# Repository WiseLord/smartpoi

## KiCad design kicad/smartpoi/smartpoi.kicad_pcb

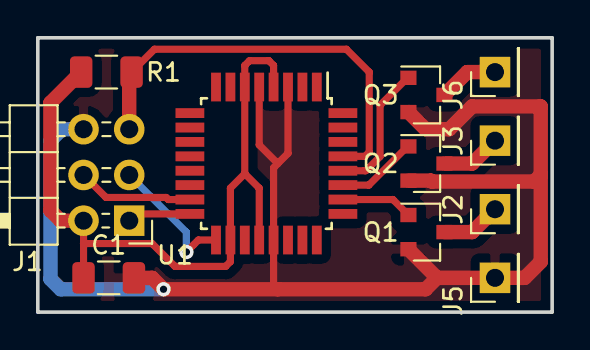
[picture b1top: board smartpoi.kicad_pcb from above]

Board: 2 copper layers, 28.6 x 15.2 mm, 11 parts (0 on the bottom side), 12 nets.

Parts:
C1: 0.1; C_1206_3216Metric
J1: AVR-ISP-6; PinHeader_2x03_P2.54mm_Horizontal
J2: K_RED; PinHeader_1x01_P2.54mm_Vertical
J3: K_GREEN; PinHeader_1x01_P2.54mm_Vertical
J5: GND; PinHeader_1x01_P2.54mm_Vertical
J6: K_BLUE; PinHeader_1x01_P2.54mm_Vertical
Q1, Q2, Q3: IRLML6244TRPBF; SOT-23
R1: 47k; R_1206_3216Metric
U1: ATmega328P-AU; TQFP-32_7x7mm_P0.8mm

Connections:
+3V8: C1.1, J1.2, R1.1, U1.4, U1.6, U1.18, U1.20
/BLUE: Q3.1, U1.28
/GREEN: Q2.1, U1.27
/K_BLUE: J6.1, Q3.3
/K_GREEN: J3.1, Q2.3
/K_RED: J2.1, Q1.3
/MISO: J1.1, U1.16
/MOSI: J1.4, U1.15
/RED: Q1.1, U1.26
/SCK: J1.3, U1.17
/~RST: J1.5, R1.2, U1.29
GNDD: C1.2, J1.6, J5.1, Q1.2, Q2.2, Q3.2, U1.3, U1.5, U1.21

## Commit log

2019-03-06 Initial commit based on ledgarland project
2019-03-09 Switch to Arduino Leonardo base
2019-03-09 Test program-based effect
2019-03-10 Support of programs-images made by lcd-image-converter
2019-03-11 Faster functions to calculate poi leds
2019-03-11 Compat programs to 75%
2019-03-16 Switch to ATmega328
2019-03-17 Add prog/effect switch functionality
2019-03-17 Add more programs
2019-03-17 Remove test color effect
